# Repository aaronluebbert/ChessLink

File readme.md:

# ChessLink

**A smart chessboard built from scratch: custom PCBs, 64 Hall-effect sensors, 64 RGB LEDs, and an ESP32 running FreeRTOS. It plays over the board against a friend, against Stockfish, or against real opponents on Lichess.**

-lightgrey)

Built for the Microcontroller Lab at Texas Tech University, Summer 2026, as a three-person group project. Inspired by commercial boards like ChessUp 2.

You move a real piece. Magnets in the piece bases trigger a sensor under each square, the firmware works out which legal move you made, and the LEDs under the board guide you. Lift a piece and its legal destinations light up. When an online opponent moves, the from and to squares light up for you to replay. Put a piece somewhere illegal and the square flashes red.

---

## Contents

- [What it does](#what-it-does)
- [A game, start to finish](#a-game-start-to-finish)
- [Hardware](#hardware)
- [Firmware](#firmware)
- [Lichess integration](#lichess-integration)
- [Repository layout](#repository-layout)
- [Build and flash](#build-and-flash)
- [First boot](#first-boot)
- [Known limitations](#known-limitations)
- [Engineering notes](#engineering-notes)
- [Team](#team)

---

## What it does

| Mode | What happens |
|---|---|
| **Local Game** | Two people play over the board. Untimed or with a clock preset (up to 30+0). Detects checkmate, stalemate, the 50-move draw, and flagging on timed games. |
| **Online Game** | Seeks a human opponent on Lichess (1+0 up to 15+10, rated or casual). Your moves are sent for you, and the opponent's moves are lit on the board for you to replay. |
| **Play Bot** | Challenges Lichess Stockfish, level 1 to 8, with a chosen clock (or untimed) and color (white, black, random). |
| **Famous Games** | Step-through study mode with five classic games stored on the device: the Immortal Game (Anderssen v Kieseritzky, 1851), the Evergreen Game (Anderssen v Dufresne, 1852), the Opera Game (Morphy, 1858), the Game of the Century (Byrne v Fischer, 1956), and Deep Blue v Kasparov (1997, game 6). The board shows each move and waits for you to play it. |
| **WiFi Setup** | Re-opens the phone-based setup page to change WiFi credentials or the Lichess token. |

Also in the box:

- **Full rules on the device.** Castling, en passant, promotion (with an on-screen piece picker), and captures are all detected from sensor occupancy alone. There is no per-piece identification.
- **Board error highlighting.** Move a piece out of turn, drop it on the wrong square, or disturb the board while waiting for an online opponent, and the offending squares light red along with where the piece should go back.
- **Start-position check.** Before each game the LEDs light every square that is still missing a piece.
- **Live match screen.** Opponent name and rating, both clocks, and a running-side indicator. Clocks tick locally and resync with the server.
- **Leave-game prompt.** Cancel mid-game opens a confirm. On a Lichess game that resigns (or aborts, early on). On a local game it just drops back to the menu.
- **Analyze on Lichess.** After a game the result screen can import the game to Lichess for analysis.
- **No credentials in the source.** WiFi and the Lichess token are entered from a phone through a captive portal and stored in flash (NVS).

---

## A game, start to finish

1. **Pick a mode** from the LCD menu with the four buttons (up, down, confirm, cancel).
2. **Set up the board.** The LEDs light green on every square that is still missing a piece for the starting position. The game begins once the sensors see the standard setup.
3. **Lift a piece.** The square lights yellow and every legal destination lights green.
4. **Put it down.** The firmware matches the new board occupancy against the legal moves from that square and commits the one that fits. The destination flashes green. A pawn reaching the last rank opens a promotion picker on the LCD.
5. **Opponent's turn.**
   - *Local:* the other player moves.
   - *Online or bot:* the move arrives from Lichess, the from square lights blue and the to square cyan, and the board waits until you have physically replayed it.
6. **Game over.** The result is shown on the LCD ("You won: mate", "Draw: stalemate", and so on). Any button returns to the menu, and online games can be sent to Lichess for analysis.

---

## Hardware

### System overview

```
                    3.7 V LiPo --> USB-C charger module (off-board)
                                        |
                        +---------------+----------------+
                        |                                |
              TLV62568 buck (3.3 V)             TLV61048 boost (5 V)
                        |                                |
          +-------------+-------------+                  |
          |   ESP32 dev board         |                  |
          |   (1.9" ST7789 LCD,       |   LED data --> 74AHCT125 --> 5 V DIN
          |    170 x 320, onboard)    |   SCLK / SR load -> 74AHCT125 -> 5 V
          |                           |   <-- 1k/2k divider <-- SR_QH (5 V)
          |   4 buttons (GPIO 34-39)  |
          +---------------------------+
                        |
        8 x Sensors+LEDs strips, one per rank, chained together:
        each has 8 x A3144 Hall sensor, 8 x WS2812B, 1 x SN74HC165
```

### Boards

Two custom two-layer PCBs, designed in KiCad 10, with JLCPCB production files (Gerbers, BOM, placement) generated in the repo.

| Board | What is on it |
|---|---|
| **ESP + Power** (35 parts) | ESP32 dev-board footprint, TLV62568 buck (3.3 V rail), TLV61048 boost (5 V rail), SN74AHCT125N level shifter, four navigation buttons, power switch, charger-module footprint, header connectors to the sensor strips. |
| **Sensors + LEDs** (41 parts, one per rank) | 8 x A3144 Hall sensors, 8 x WS2812B LEDs, 1 x SN74HC165N parallel-in shift register, decoupling, pull-ups. Eight of these make up the 8x8 board. |

Total across the board: **64 sensors and 64 LEDs**.

Custom footprints and symbols live in `pcb/ChessLink_Footprints.pretty` and `pcb/ChessLink_Symbols`.

### How a square is sensed

1. Each piece has an N52 disc magnet embedded in its base. Pieces and squares are 3D printed; the print is paused mid-way so the magnet can be dropped in and fully enclosed.
2. An A3144 Hall sensor under each square pulls its input low when a magnet is present.
3. The firmware pulses the shift-register load line, then clocks the whole 64-bit chain back in over the ESP32's VSPI bus at 1 MHz. A scan runs every 20 ms, and a change must appear in 3 consecutive scans before it is accepted.

Design-stage calculations put the field from a 10 x 3 mm N52 magnet at roughly 1,100 to 1,300 gauss at a 4.5 mm gap, about 2.5 to 3 times the A3144 trigger threshold, with adjacent-square crosstalk well below threshold at the 57 mm square pitch (within the 50 to 60 mm range in the FIDE handbook). These are calculated margins, not a measured characterization.

### Pin map

The full table is in [`rtos/chesslink/PIN_MAP.md`](rtos/chesslink/PIN_MAP.md). The short version:

| Function | GPIO |
|---|---|
| Shared SPI clock (LCD and shift registers) | 18 |
| Shift-register data in (MISO) / LCD data (MOSI) | 19 / 23 |
| Shift-register load | 5 |
| LCD CS / DC / RST / backlight | 15 / 2 / 4 / 32 |
| WS2812B data (through 74AHCT125) | 25 |
| Buttons: up / down / confirm / cancel | 36 / 39 / 34 / 35 |

---

## Firmware

About 4,200 lines of C++ on the Arduino ESP32 core, structured as six FreeRTOS tasks that communicate only through queues. No task reaches into another task's state.

```
 SensorScan --BoardState--> GameLogic --GameState--> LcdDisplay
                              |  ^  \---LedCmd-----> LedControl
 Buttons ---ButtonEvent------/   |
                                 |  NetUpdate (clocks, players, status, result)
 Network <---NetCmd--- GameLogic ^
    |  \--OpponentMove--> GameLogic
    ^----PlayerMove------ GameLogic
```

| Task | Core | Priority | Stack | Job |
|---|---|---|---|---|
| SensorScan | 1 | 5 | 4 KB | Latch and read 64 sensors, debounce, publish an occupancy bitmask |
| LedControl | 1 | 4 | 4 KB | Drive the WS2812B strip with FastLED, capped at about 60 fps |
| GameLogic | 1 | 3 | 8 KB | Rules, move detection, UI state, game flow |
| Buttons | 1 | 3 | 2 KB | Debounce four active-low buttons |
| Network | 0 | 2 | 16 KB | WiFi, captive portal, Lichess HTTP and streaming |
| LcdDisplay | 0 | 1 | 8 KB | Render every screen to the ST7789 |

Real-time I/O and game logic sit on core 1. The WiFi stack and anything that can block on the network sit on core 0.

### Design decisions worth calling out

- **Move detection by expected occupancy.** When a piece is lifted, the engine precomputes the board occupancy that each legal move from that square would produce. The move is committed when the sensors settle on one of those patterns. That makes captures, castling, en passant, and promotion fall out naturally, since the board is compared as a whole rather than square by square.
- **Opponent-move reconciliation.** When a Lichess opponent moves, the firmware updates its own position, lights the from and to squares, and holds until the physical board matches before handing the turn back.
- **Server position wins.** Online, the move list from Lichess is rebuilt into a FEN and adopted as truth, so the on-device position cannot drift from the game.
- **On-device chess engine.** A bitboard move generator with legal-move filtering, make and unmake, FEN in and out, and UCI conversion (`chess_engine.cpp`, about 700 lines). Move legality does not depend on a server or a Raspberry Pi.
- **One SPI bus, two devices.** The LCD and the shift-register chain share SCK. Both tasks hold a mutex around bus access so a display write cannot interleave with a sensor read.
- **Canonical square index.** `sq = rank * 8 + file` (a1 = 0, h8 = 63) everywhere. Physical wiring order is isolated in `board_map.h` and one function in `task_sensor.cpp`.

---

## Lichess integration

Uses the Lichess Board API over HTTPS. Authentication is a personal API token (`board:play` scope) entered at setup and stored in flash.

| Purpose | Endpoint |
|---|---|
| Find an online opponent | `POST /api/board/seek` |
| Stream a game (moves, clocks, result) | `GET /api/board/game/stream/{id}` |
| Send your move | `POST /api/board/game/{id}/move/{uci}` |
| Resign or abort | `POST /api/board/game/{id}/resign` or `/abort` |
| Play Stockfish | `POST /api/challenge/ai` |
| Export a finished game for analysis | `POST /api/import` |

---

## Repository layout

```
ChessLink/
  rtos/chesslink/              Arduino sketch (open chesslink.ino)
    main.cpp                   queue and task creation
    chesslink.h                pins, task config, shared types
    chess_engine.{h,cpp}       bitboard rules engine
    task_sensor.cpp            shift-register read and debounce
    task_led.cpp               WS2812B control
    task_game.cpp              game logic, move detection, menus
    task_display.cpp           ST7789 rendering
    task_network.cpp           WiFi, captive portal, Lichess
    task_buttons.cpp           button debounce
    board_map.h                square-to-LED mapping
    PIN_MAP.md                 firmware to PCB pin map
    FILE_REFERENCE.md          per-file design notes
    BUILD_AND_FLASH.md         IDE setup, board settings, flashing, troubleshooting
  pcb/
    ChessLink_Footprints.pretty/   custom KiCad footprints
    ChessLink_Symbols/             custom KiCad symbols
    Microcontroller Lab Summer 2026/
      ESP+Power_Only/          control and power board (KiCad + production files)
      Sensors+LEDs/            per-rank sensor and LED strip (KiCad + production files)
```

---

## Build and flash

Requirements: Arduino IDE 2.x and the **esp32 by Espressif** board package.

Libraries (Library Manager):

- GFX Library for Arduino (`Arduino_GFX_Library`)
- FastLED
- ArduinoJson 6.x

`WiFi`, `HTTPClient`, `WebServer`, `DNSServer`, `Preferences`, and `SPI` ship with the ESP32 core.

Steps:

1. Open `rtos/chesslink/chesslink.ino`. The IDE compiles every `.cpp` in the folder.
2. Board: **ESP32 Dev Module**.
3. Partition scheme: **Huge APP (3MB No OTA/1MB SPIFFS)**. WiFi, TLS, and the HTTP client need the room.
4. Enable **PSRAM** if your module has it.
5. Upload. If it will not enter the bootloader, hold BOOT, tap EN, and release BOOT once "Connecting..." appears.

---

## First boot

1. With no saved WiFi, the board starts an access point called `ChessLink-Setup` and shows instructions on the LCD.
2. Join it from a phone. A setup page opens automatically, or go to `192.168.4.1`.
3. Pick your WiFi network, enter its password, and paste a Lichess API token. Create one at lichess.org under Preferences, API access tokens, with the `board:play` scope.
4. The board saves everything to flash, connects, and lands on the menu. You only do this once; **WiFi Setup** in the menu reopens it. A bad token is not validated at setup, so it only shows up as a failed seek or bot start.

The setup access point uses a fixed default password, defined in `chesslink.h`. Change it before leaving a board running anywhere untrusted.

---

## Known limitations

Things this build does not do:

- **No automated tests are committed.** The engine and move-detection logic were checked during development, but no test suite is in this repo.
- **LED brightness is conservative.** It is set to 48 of 255 pending a thermal check of the full 64-LED load.
- **Not implemented:** resuming a game after a reboot, persistent settings, a check highlight, draw offers and takebacks, puzzle mode, and OTA updates.

---

## Engineering notes

- **A software bug that looked like a hardware fault.** One rank of the board kept misbehaving. I replaced that entire sensor strip before finding the cause was a mapping error in the LED and sensor index tables. I moved to explicit, editable lookup tables during bring-up so a single wrong rank is a one-line fix.
- **Shared-clock bring-up bug.** With four parallel segments sharing one clock, reading them one after another corrupted the later segments, because the shared clock had already shifted their data out. The fix was to sample all lines on the same clock edges, and later to move to a single 64-bit daisy chain.
- **Off-by-one on the first square.** The '165 presents square a1 on the data line right after the load pulse, before any clock edge. The SPI master misses it, which shifts the whole board by one square. `sr_read_all()` reads that first bit directly and shifts the rest into place.
- **Input-only GPIOs have no internal pull-ups.** The four buttons on GPIO 34, 35, 36, and 39 need external 10 k pull-ups, which are on the main board.
- **Identical-looking pieces on the LCD.** An early display bug drew every piece as the same white circle, so the board view was unreadable. Rendering the piece letter inside each circle, taken from the FEN, fixed it.

---

## Team

ChessLink was a group project by **Gabriel Cooper**, **Aaron Luebbert**, and **Nnamdi Onyejekwe**.

My part (Aaron): the PCB design in KiCad (schematics, custom footprints and symbols, layout, production files and ordering), the FreeRTOS firmware architecture and integration, and hardware bring-up and debugging. The WiFi captive-portal page and the menu and Stockfish-picker layout began as teammates' prototypes and were folded into this firmware.

Thanks to Jordie Bellar, for all the help and inspiration.

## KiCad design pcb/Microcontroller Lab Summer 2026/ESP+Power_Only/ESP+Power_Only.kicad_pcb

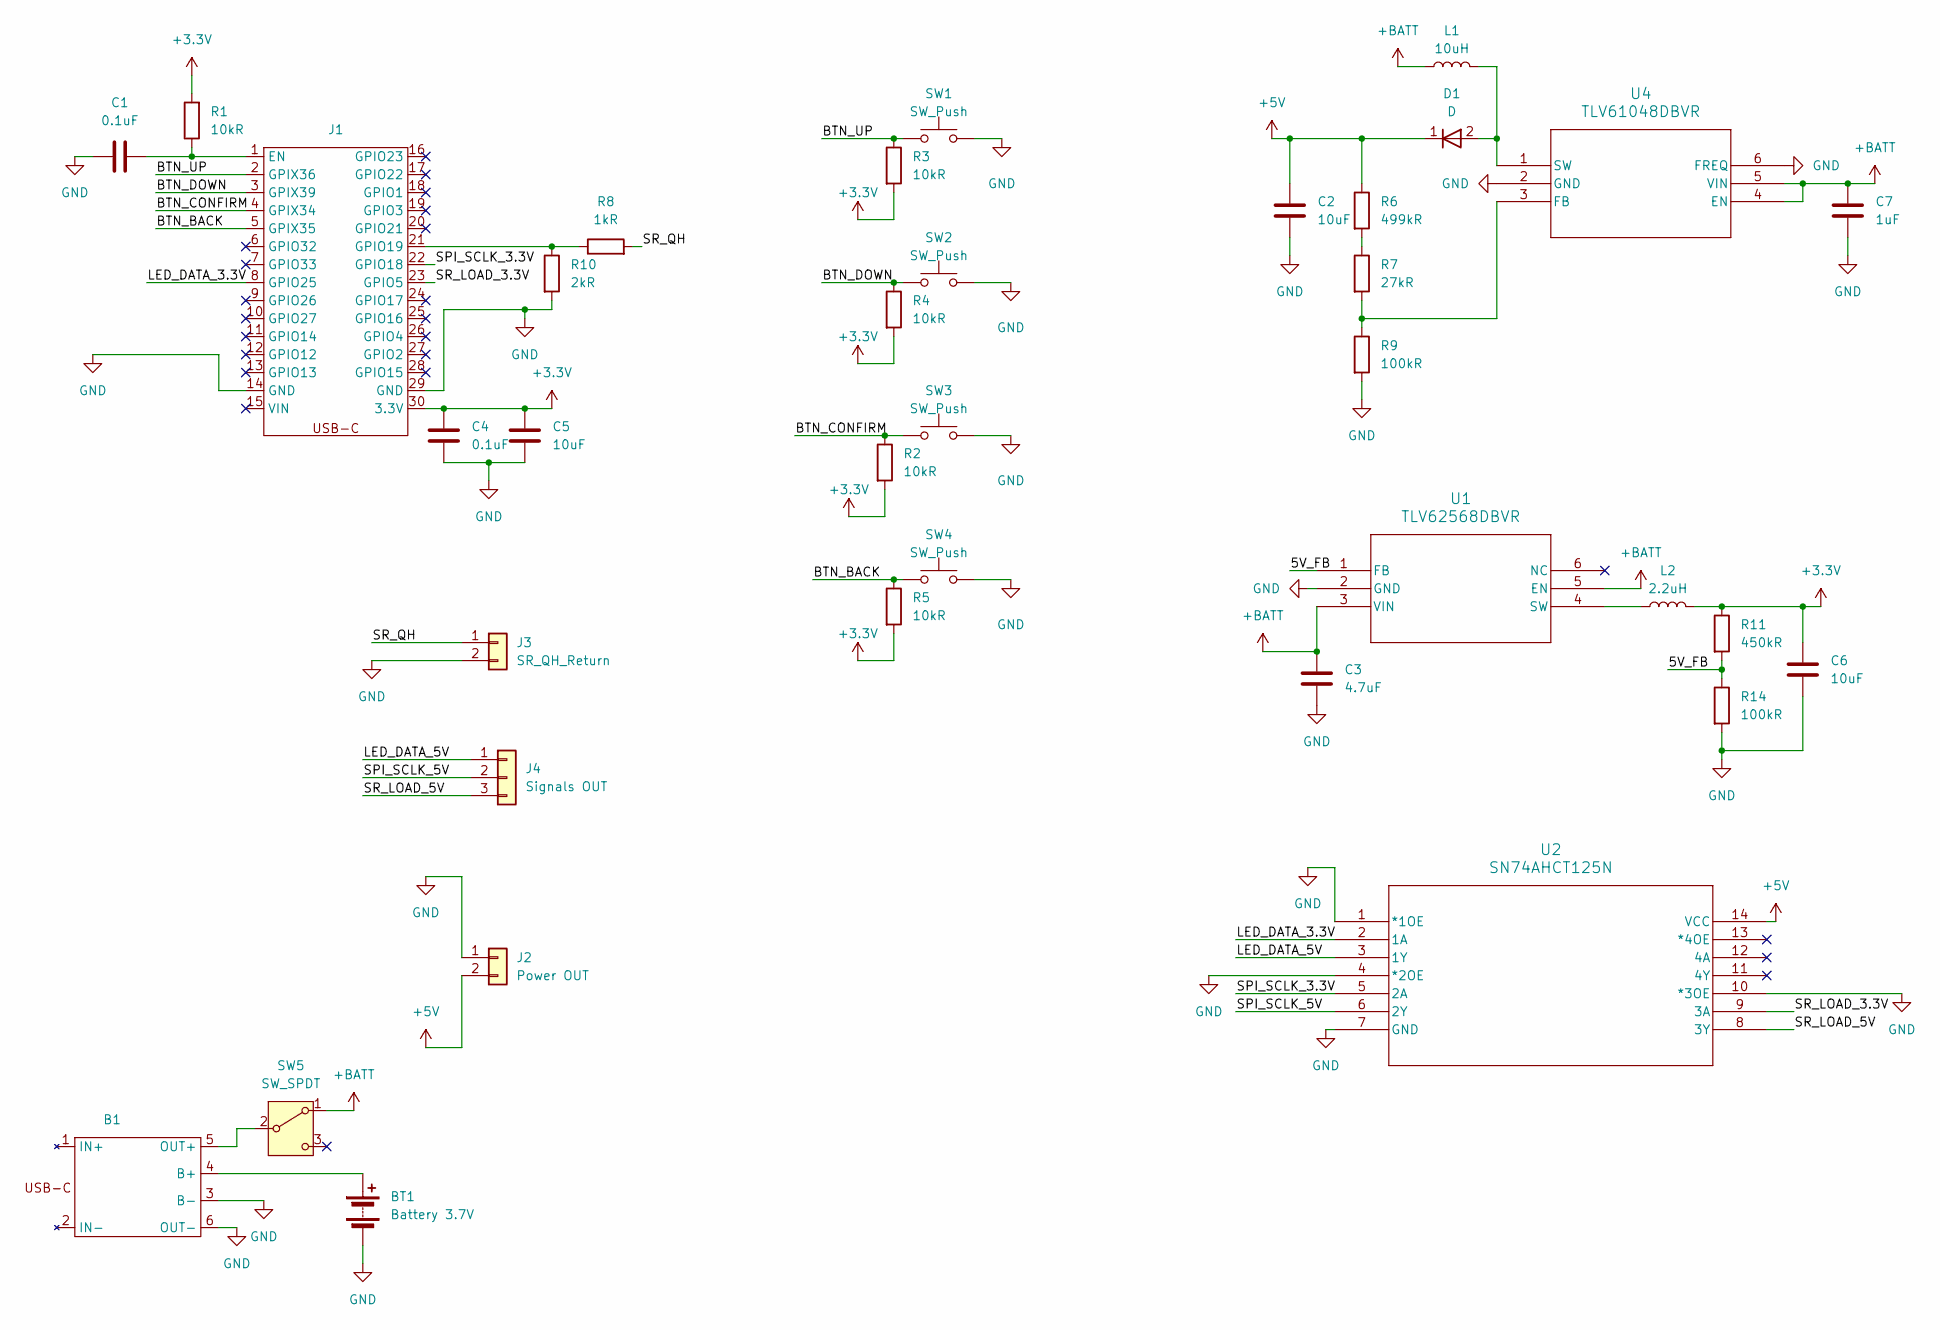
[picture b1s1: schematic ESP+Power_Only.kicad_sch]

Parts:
B1: Battery_Charger_Board
BT1: Battery 3.7V
C1, C4: 0.1uF; C_0402_1005Metric; LCSC C1525
C2, C5, C6: 10uF; C_0603_1608Metric; LCSC C1691
C3: 4.7uF; C_0603_1608Metric; LCSC C1705
C7: 1uF; C_0603_1608Metric; LCSC C1592
D1: D; ChessLink_Schottky_Diode; LCSC C8678
J1: ESP
J2: Power OUT; Pin header spacing
J3: SR_QH_Return; PinHeader_1x02_P2.54mm_Vertical
J4: Signals OUT; PinHeader_1x03_P2.54mm_Vertical
L1: 10uH; ChessLink_10uH_Inductor; LCSC C181721
L2: 2.2uH; ChessLink_2.2uH_Inductor; LCSC C133191
R1, R2, R3, R4, R5: 10kR; R_1206_3216Metric; LCSC C17902
R6: 499kR; R_0402_1005Metric; LCSC C25793
R7: 27kR; R_1206_3216Metric; LCSC C1498
R8: 1kR; R_1206_3216Metric; LCSC C1469
R9, R14: 100kR; R_0603_1608Metric; LCSC C1996
R10: 2kR; R_0805_2012Metric; LCSC C1359
R11: 450kR; R_0402_1005Metric; LCSC C5159688
SW1, SW2, SW3, SW4: SW_Push; SW_TH_Tactile_Omron_B3F-100x
SW5: SW_SPDT; Switch
U1: TLV62568DBVR; LCSC C163219
U2: SN74AHCT125N; DIP-14_W7.62mm_LongPads
U4: TLV61048DBVR; LCSC C2861467

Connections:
+3.3V: C4.2, C5.2, C6.1, J1.30 (3.3V), L2.2, R1.2, R2.2, R3.2, R4.2, R5.2, R11.1
+5V: C2.1, D1.1 (K), J2.2, R6.1, U2.14 (VCC)
+BATT: C3.1, C7.1, L1.1, SW5.1 (A), U1.3 (VIN), U1.5 (EN), U4.4 (EN), U4.5 (VIN)
/5V_FB: R11.2, R14.1, U1.1 (FB)
/BTN_BACK: J1.5 (GPIX35), R5.1, SW4.1
/BTN_CONFIRM: J1.4 (GPIX34), R2.1, SW3.1
/BTN_DOWN: J1.3 (GPIX39), R4.1, SW2.1
/BTN_UP: J1.2 (GPIX36), R3.1, SW1.1
/LED_DATA_3.3V: J1.8 (GPIO25), U2.2 (1A)
/LED_DATA_5V: J4.1, U2.3 (1Y)
/SPI_SCLK_3.3V: J1.22 (GPIO18), U2.5 (2A)
/SPI_SCLK_5V: J4.2, U2.6 (2Y)
/SR_LOAD_3.3V: J1.23 (GPIO5), U2.9 (3A)
/SR_LOAD_5V: J4.3, U2.8 (3Y)
/SR_QH: J3.1, R8.2
GND: B1.3 (B-), B1.6 (OUT-), BT1.2 (-), C1.1, C2.2, C3.2, C4.1, C5.1, C6.2, C7.2, J1.14 (GND), J1.29 (GND), J2.1, J3.2, R9.2, R10.2, R14.2, SW1.2, SW2.2, SW3.2, SW4.2, U1.2 (GND), U2.1 (*1OE), U2.4 (*2OE), U2.7 (GND), U2.10 (*3OE), U4.2 (GND), U4.6 (FREQ)
unnamed: B1.4 (B+), BT1.1 (+)
unnamed: B1.5 (OUT+), SW5.2 (B)
unnamed: D1.2 (A), L1.2, U4.1 (SW)
unnamed: C1.2, J1.1 (EN), R1.1
unnamed: J1.21 (GPIO19), R8.1, R10.1
unnamed: R6.2, R7.1
unnamed: L2.1, U1.4 (SW)
unnamed: R7.2, R9.1, U4.3 (FB)

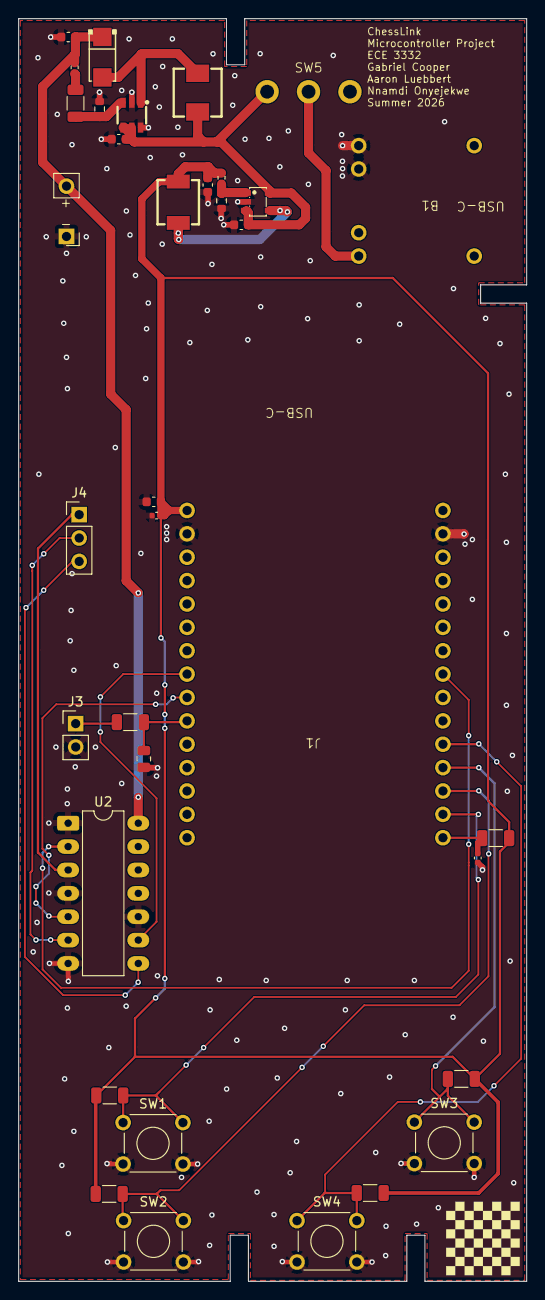
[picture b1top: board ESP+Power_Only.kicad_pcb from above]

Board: 2 copper layers, 55.2 x 137.2 mm, 35 parts (0 on the bottom side), 23 nets.

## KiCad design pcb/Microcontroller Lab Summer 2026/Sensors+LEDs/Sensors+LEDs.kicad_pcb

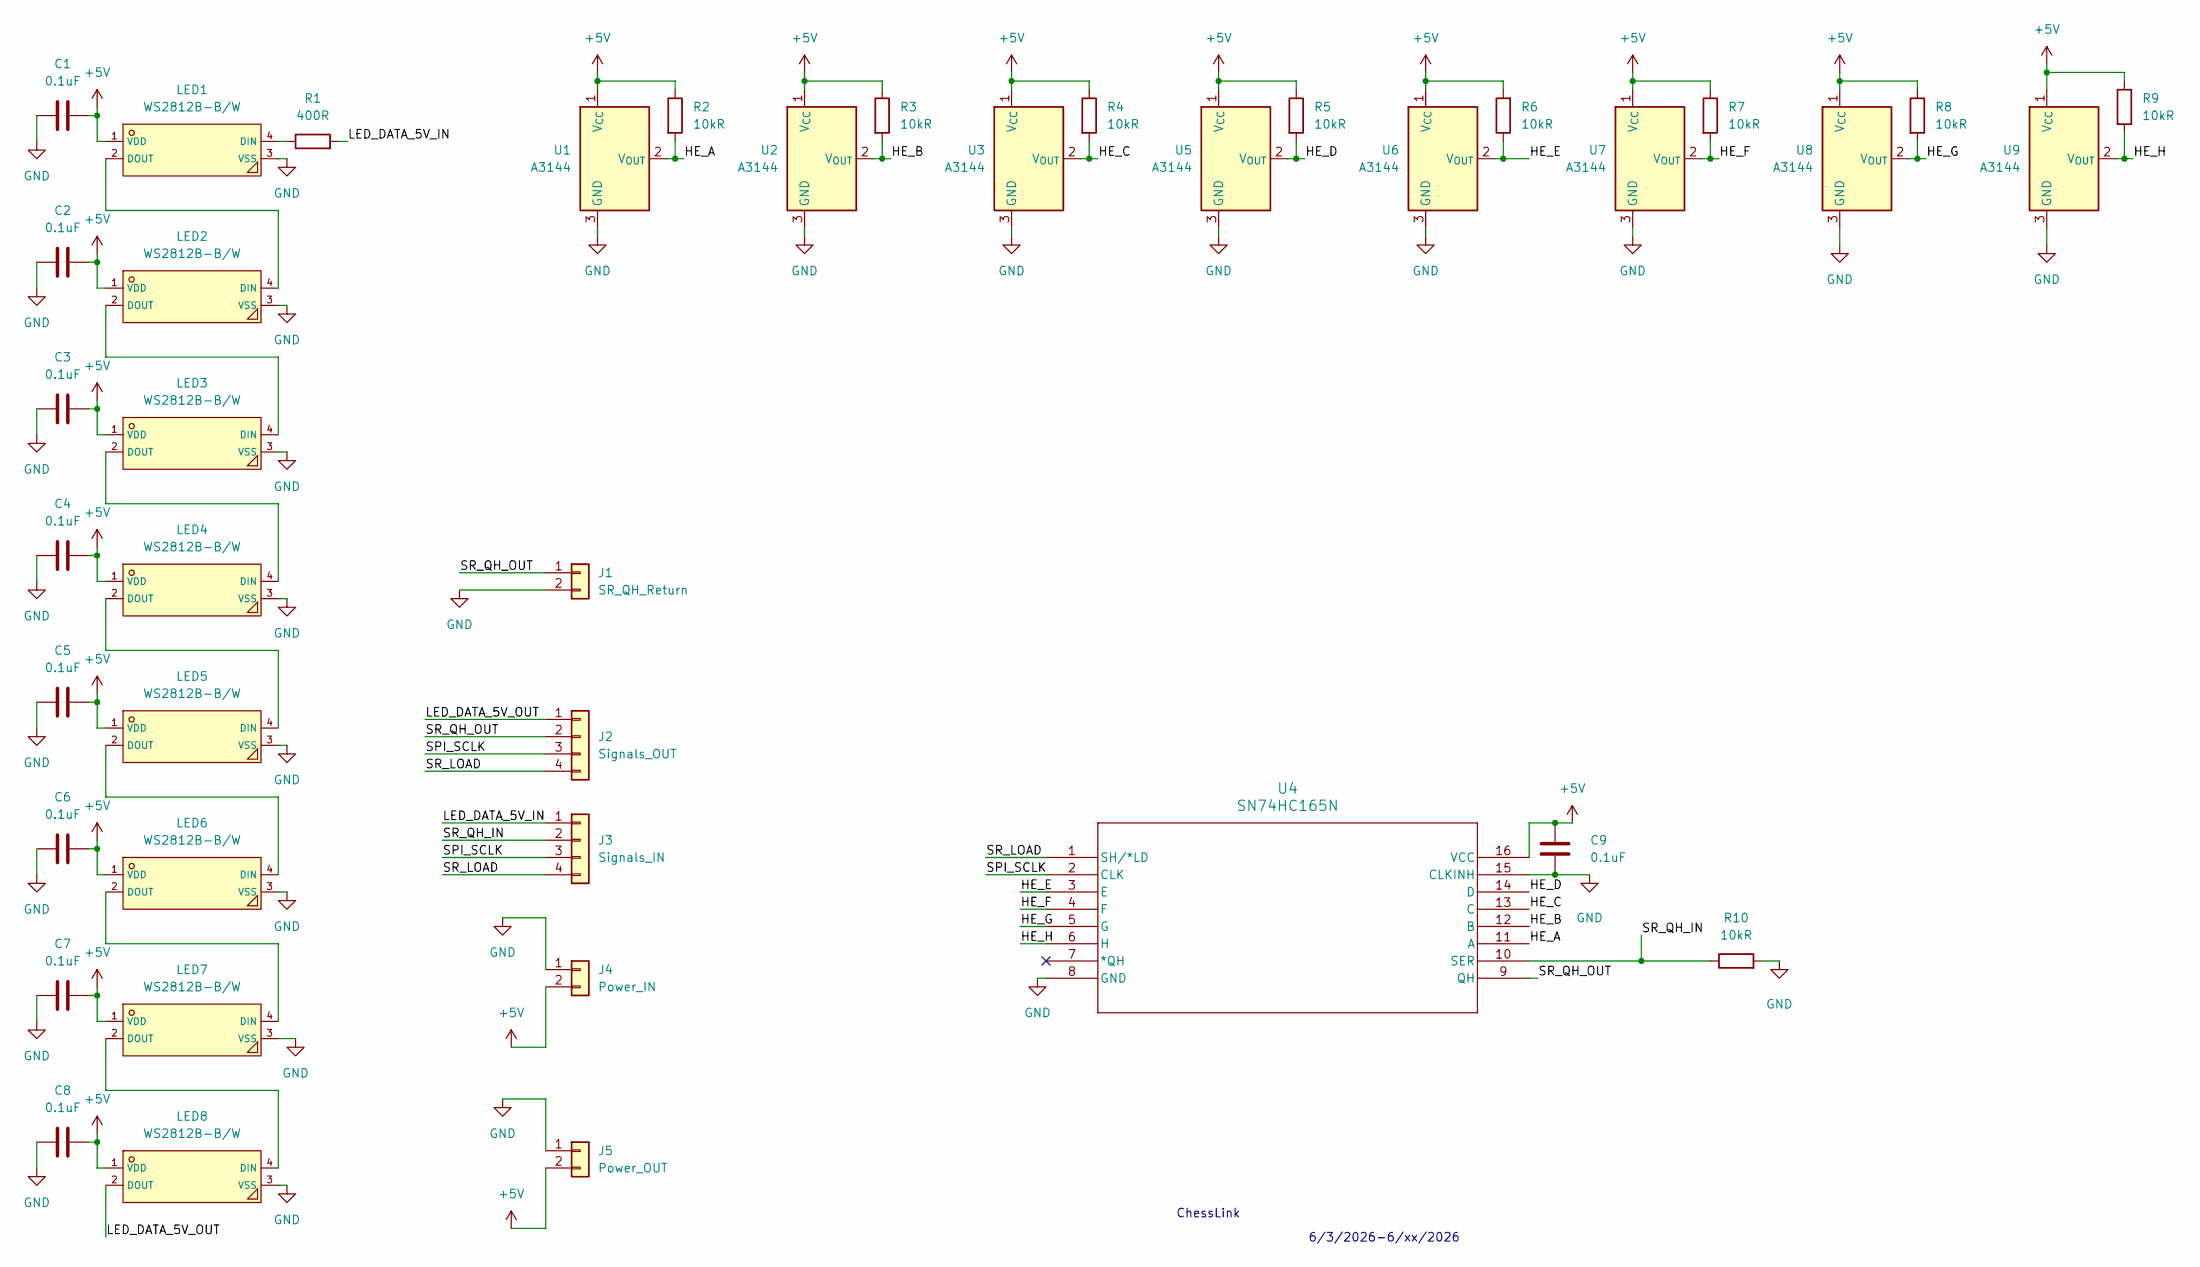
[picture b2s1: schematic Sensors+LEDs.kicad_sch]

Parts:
C1, C2, C3, C4, C5, C6, C7, C8, C9: 0.1uF; C_0402_1005Metric; LCSC C1525
J1: SR_QH_Return; PinHeader_1x02_P2.54mm_Vertical
J2: Signals_OUT; PinHeader_1x04_P2.54mm_Vertical
J3: Signals_IN; PinHeader_1x04_P2.54mm_Vertical
J4: Power_IN; Pin header spacing
J5: Power_OUT; Pin header spacing
LED1, LED2, LED3, LED4, LED5, LED6, LED7, LED8: WS2812B-B/W; WS2812B-B_W; LCSC C2761795
R1: 400R; R_1206_3216Metric; LCSC C706413
R2, R3, R4, R5, R6, R7, R8, R9, R10: 10kR; R_1206_3216Metric; LCSC C17902
U1, U2, U3, U5, U6, U7, U8, U9: A3144
U4: SN74HC165N; DIP-16_W7.62mm_LongPads

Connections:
+5V: C1.2, C2.2, C3.2, C4.2, C5.2, C6.2, C7.2, C8.2, C9.1, J4.2, J5.2, LED1.1 (VDD), LED2.1 (VDD), LED3.1 (VDD), LED4.1 (VDD), LED5.1 (VDD), LED6.1 (VDD), LED7.1 (VDD), LED8.1 (VDD), R2.1, R3.1, R4.1, R5.1, R6.2, R7.1, R8.1, R9.1, U1.1 (V_{CC}), U2.1 (V_{CC}), U3.1 (V_{CC}), U4.16 (VCC), U5.1 (V_{CC}), U6.1 (V_{CC}), U7.1 (V_{CC}), U8.1 (V_{CC}), U9.1 (V_{CC})
/HE_A: R2.2, U1.2 (V_{OUT}), U4.11 (A)
/HE_B: R3.2, U2.2 (V_{OUT}), U4.12 (B)
/HE_C: R4.2, U3.2 (V_{OUT}), U4.13 (C)
/HE_D: R5.2, U4.14 (D), U5.2 (V_{OUT})
/HE_E: R6.1, U4.3 (E), U6.2 (V_{OUT})
/HE_F: R7.2, U4.4 (F), U7.2 (V_{OUT})
/HE_G: R8.2, U4.5 (G), U8.2 (V_{OUT})
/HE_H: R9.2, U4.6 (H), U9.2 (V_{OUT})
/LED_DATA_5V_IN: J3.1, R1.2
/LED_DATA_5V_OUT: J2.1, LED8.2 (DOUT)
/SPI_SCLK: J2.3, J3.3, U4.2 (CLK)
/SR_LOAD: J2.4, J3.4, U4.1 (SH/*LD)
/SR_QH_IN: J3.2, R10.1, U4.10 (SER)
/SR_QH_OUT: J1.1, J2.2, U4.9 (QH)
GND: C1.1, C2.1, C3.1, C4.1, C5.1, C6.1, C7.1, C8.1, C9.2, J1.2, J4.1, J5.1, LED1.3 (VSS), LED2.3 (VSS), LED3.3 (VSS), LED4.3 (VSS), LED5.3 (VSS), LED6.3 (VSS), LED7.3 (VSS), LED8.3 (VSS), R10.2, U1.3 (GND), U2.3 (GND), U3.3 (GND), U4.8 (GND), U4.15 (CLKINH), U5.3 (GND), U6.3 (GND), U7.3 (GND), U8.3 (GND), U9.3 (GND)
unnamed: LED1.4 (DIN), R1.1
unnamed: LED1.2 (DOUT), LED2.4 (DIN)
unnamed: LED2.2 (DOUT), LED3.4 (DIN)
unnamed: LED3.2 (DOUT), LED4.4 (DIN)
unnamed: LED4.2 (DOUT), LED5.4 (DIN)
unnamed: LED5.2 (DOUT), LED6.4 (DIN)
unnamed: LED6.2 (DOUT), LED7.4 (DIN)
unnamed: LED7.2 (DOUT), LED8.4 (DIN)

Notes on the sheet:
ChessLink
6/3/2026-6/xx/2026

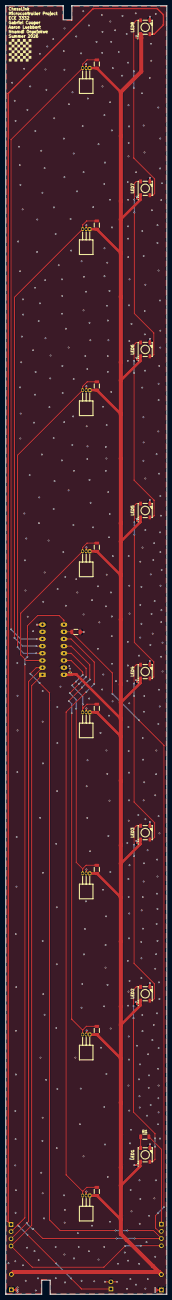
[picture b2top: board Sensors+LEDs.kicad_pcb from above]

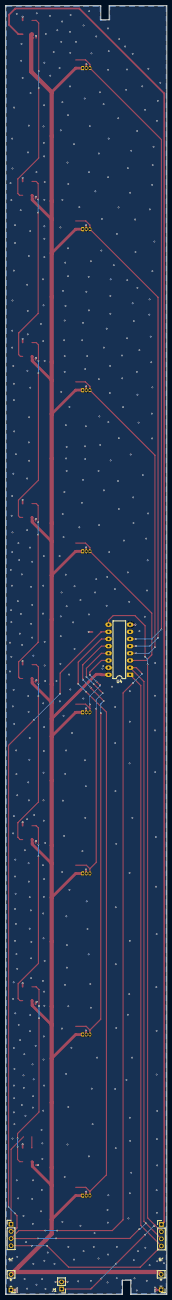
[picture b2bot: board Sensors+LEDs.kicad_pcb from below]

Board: 2 copper layers, 57.1 x 456.8 mm, 41 parts (6 on the bottom side), 24 nets.

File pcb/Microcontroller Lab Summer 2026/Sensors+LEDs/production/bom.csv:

Designator,Footprint,Quantity,Value,LCSC Part #
"C1, C2, C3, C4, C5, C6, C7, C8, C9",0402,9,0.1uF,C1525
J1,PinHeader_1x02_P2.54mm_Vertical,1,SR_QH_Return,
J2,PinHeader_1x04_P2.54mm_Vertical,1,Signals_OUT,
J3,PinHeader_1x04_P2.54mm_Vertical,1,Signals_IN,
J4,Pin header spacing,1,Power_IN,
J5,Pin header spacing,1,Power_OUT,
"LED1, LED2, LED3, LED4, LED5, LED6, LED7, LED8",WS2812B-B_W,8,WS2812B-B/W,C2761795
R1,1206,1,400R,C706413
"R10, R2, R3, R4, R5, R6, R7, R8, R9",1206,9,10kR,C17902
"U1, U2, U3, U5, U6, U7, U8, U9",A3144,8,A3144,
U4,DIP-16_W10.16mm_LongPads,1,SN74HC165N,

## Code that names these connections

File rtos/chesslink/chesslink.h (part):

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// --- pin definitions ---------------------------------------------------------

// SN74HC165 shift registers -- read over the VSPI hardware bus (SR_SCLK/SR_MISO
// are VSPI SCK/MISO, shared with the LCD; see below). SR_LOAD is a plain GPIO
// latch. the ideaspark board wires these to the ESP32 default VSPI pins
#define SR_SCLK       18   // VSPI SCK, shared with the LCD
#define SR_MISO       19   // VSPI MISO -- QH from the SR chain
#define SR_LOAD       5    // parallel load (PL), active-low, bit-banged latch

// WS2812B via 74AHCT125 level shifter
#define LED_DATA_PIN  25   // RMT output -> level shifter -> LED_DATA_5V

// ST7789 LCD (170x320) on the SAME VSPI bus as the shift registers. the LCD
// writes on MOSI, the SR reads on MISO, both clocked by SCLK 18. the sensor and
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#define LCD_BL        32

// tactile buttons (input-only pins, no internal pullup -- needs external 10k to 3.3V)
#define BTN_UP        36   // menu up / previous
#define BTN_DOWN      39   // menu down / next
#define BTN_CONFIRM   34   // confirm / select
#define BTN_CANCEL    35   // cancel / back

// --- board geometry ----------------------------------------------------------
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extern QueueHandle_t xQ_NetCmd;
extern QueueHandle_t xQ_NetUpdate;

// serializes access to the shared SR/LCD clock net (GPIO18): the sensor and the
// display each hold it while bit-banging so their edges never interleave
extern SemaphoreHandle_t xSPI18Mutex;

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
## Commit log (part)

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2026-06-02 init commit
2026-06-10 Yeah guys I dont think this work
    booogggi e
2026-06-10 This one may work guys
    idk yet
2026-06-11 Connection to Wifi and verifies API token.
    Used Claude to get this going. requires inputs from serial monitor. Wifi name, wifi password, and the API token. Wifi connection is finicky though. I had to make my hotspot name all lowercase and the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
2026-06-11 Auto-Saved Wifi and API tokens
    This code will allow you to save wifi and api settings into the esp32 so that resets don't re-prompt everything. The device will automatically connect to the wifi if available then log into lichess a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
2026-06-11 Instructions
2026-06-11 Menu Gui + WIFI + API
    Mkay, so basically "w" and "s" command prompts move the menu selector. Wifi and API connectivity flash available still and clearing. Less diagnostic messages in serial monitor and lcd display.
2026-06-12 GUI with serial monitor commands
2026-06-12 Better
2026-06-27 first rtos version
2026-06-28 updated rtos logic to account for pcb ssetup decisions
2026-06-28 pcb files added. added .gitignore for kicad backup files and lock files
2026-06-28 reshuffled task assignments
2026-06-29 removed failed_sketch.ino
2026-06-29 CONNECT IT ALL
    This is everything incorporated file
